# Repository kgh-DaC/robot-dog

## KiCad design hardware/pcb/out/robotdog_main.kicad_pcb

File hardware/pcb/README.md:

# 로봇개 메인 보드 PCB (50 × 70 mm, 2층)

`회로도.jpg`(Fritzing 배선도)를 기판 하나로 옮긴 것이다. 모듈(ESP32 30핀 DevKit, MPU9250, INA219, Mini360 ×3)은 그대로 꽂거나 납땜하고, 서보 12개는 3핀 헤더로 연결한다.

| 파일 | 용도 |
| --- | --- |
| `make_pcb.py` | 부품 연결·배치·배선이 모두 들어 있는 생성 스크립트. 실행하면 아래 파일을 다시 만들고 간격·연결 검사를 한다 |
| `out/robotdog_main_gerber.zip` | **PCB 주문용** (Gerber 7장 + 드릴 2장). JLCPCB 등에 그대로 올린다 |
| `out/robotdog_main.kicad_pcb` | KiCad 8에서 열어 고칠 수 있는 보드 파일 (GND 면은 열고 `B` 키로 채움) |
| `out/robotdog_main_top.png`, `_bottom.png` | 미리보기 (주황 = 윗면 구리, 파랑 = 아랫면 구리, 점선 = ESP32 보드 위치) |

**v2 (2026-11-16)**: ESP32를 30핀 보드(핀 줄 간격 25.4 mm, 사용자 확인)로 바꿈. 서보 헤더마다 관절 표시 추가.

다시 만들기: `pip install shapely matplotlib` 후 `python make_pcb.py`. 마지막 줄이 `DRC: no clearance / connectivity errors`여야 한다.

## 회로 (회로도.jpg와 같음, 바뀐 점은 굵게)

```
배터리(2×18650) + ─ 스위치(기판 밖) ─ J1 + ─ INA219 VIN+ ─(션트)─ VIN- ─┬─ PS1 Mini360 → 5.2 V → ESP32 VIN 핀, C1
배터리 -  ─────────────────────────── J1 - (GND)                        ├─ PS2 Mini360 → 6 V → 왼쪽 서보 6개(LF, LH), C2
                                                                         └─ PS3 Mini360 → 6 V → 오른쪽 서보 6개(RF, RH), C3
ESP32 3V3 → MPU9250 VCC, INA219 VCC        I2C: SDA = GPIO21, SCL = GPIO22 (MPU9250, INA219 공용)
MPU9250 AD0 → GND  (요청대로 선을 추가함. 주소 0x68 고정)
```

- **AD0-GND**: 윗면에 MPU9250 AD0 핀에서 같은 모듈의 GND 핀까지 배선이 있다 (핀 줄 왼쪽으로 돌아감). 실크에 `AD0=GND`라고 적혀 있다. INA219(0x40)와 주소가 겹치지 않는다.
- **추가한 것**: 서보 전원마다 1000 µF 콘덴서(C2, C3). 기록상 `reset=BROWNOUT`이 잦아서 넣었다. 필요 없으면 비워 둬도 된다.
- **스위치**: 회로도처럼 기판 밖에 둔다. 배터리 +는 스위치로 가고, 스위치 다른 쪽을 J1 +에 연결한다.

### 서보 핀 (펌웨어 `servoInitPose.ino`의 `servos[]` 그대로)

| 다리 | ALPHA | BETA | GAMMA | 기판 위치 |
| --- | --- | --- | --- | --- |
| LF (왼앞) | 25 | 26 | 27 | 왼쪽 헤더 위 3개 |
| LH (왼뒤) | 13 | 12 | 14 | 왼쪽 헤더 아래 3개 |
| RF (오른앞) | 16 | 18 | 17 | 오른쪽 헤더 위 3개 |
| RH (오른뒤) | 4 | 2 | 15 | 오른쪽 헤더 아래 3개 |

헤더 핀 순서: 안쪽(ESP32 쪽)부터 **S(신호) · + · -**. 서보 커넥터의 갈색(또는 검은색) 선이 바깥쪽 `-`로 가야 한다.

실크 표시: 헤더마다 안쪽에 **관절 글자 + GPIO** (`A25` = ALPHA·GPIO25, `B` = BETA, `G` = GAMMA). 바깥 가장자리에 다리 이름(LF, LH, RF, RH)이 있고, 두 다리 묶음 사이에 짧은 가로선이 있다. 왼쪽 아래에 `A:ALPHA B:BETA G:GAMMA` 설명이 있다.

| 헤더 | 위 → 아래 |
| --- | --- |
| 왼쪽 | LF: A25 B26 G27 ─ LH: G14 B12 A13 |
| 오른쪽 | RF: B18 (빈 칸) G17 A16 ─ RH: A4 B2 G15 |

## 부품 목록

| 기호 | 부품 | 수량 | 비고 |
| --- | --- | --- | --- |
| U1 | ESP32 DevKit V1 30핀 + 1×15 암 헤더 | 1 + 2 | 두 줄 간격 25.4 mm. 암 헤더 위에 꽂는다 (아래에 PS1, MPU9250이 들어감) |
| U2 | MPU9250 모듈 (GY-9250) | 1 | 1×10 수 헤더로 바로 납땜 |
| U3 | INA219 모듈 (Adafruit 904 핀 순서) | 1 | 1×6 수 헤더로 바로 납땜. **나사 단자는 달지 않는다** |
| PS1–PS3 | Mini360 강압 모듈 | 3 | 짧은 철사 다리(저항 다리 자투리)로 납땜 |
| J1 | 2핀 나사 단자 3.5 mm (KF350-2P) | 1 | 배터리 입력 (스위치 뒤) |
| J2–J13 | 1×3 수 핀 헤더 2.54 mm | 12 | 서보 |
| C1 | 470 µF 10 V 전해 (지름 6.3 mm, 높이 8 mm 이하) | 1 | ESP32 아래에 들어가므로 낮은 것 |
| C2, C3 | 1000 µF 10 V 전해 (지름 8 mm) | 2 | 선택 |
| H1–H3 | M3 장착 구멍 | 3 | 오른쪽 아래 모서리는 J1이 차지 |

기판 주문 설정: 2층, 1.6 mm, 구리 1 oz, 최소 선폭·간격 0.3 mm, 비아 0.4/0.8 mm. 전원선 폭은 2.0 mm(배터리·강압 입력), 1.5–2.0 mm(서보 전원, 위·아래 두 층), 1.0 mm(5 V)다.

## 꼭 확인할 것 (추정한 치수)

모듈 치수는 판매처마다 다르다. **주문 전에 갖고 있는 모듈을 자로 재서** 아래 값과 맞는지 본다. 다르면 `make_pcb.py` 앞부분 숫자를 고쳐 다시 실행한다.

1. **ESP32 30핀 보드**: 두 핀 줄 간격 25.4 mm (사용자 실측 확인). 핀 배열은 안테나를 위로 두고 왼쪽 위부터 EN, VP, VN, 34, 35, 32, 33, 25, 26, 27, 14, 12, 13, GND, VIN / 오른쪽 위부터 23, 22, TX, RX, 21, 19, 18, 5, 17, 16, 4, 2, 15, GND, 3V3 이어야 한다.
2. **Mini360 패드 위치**: 17.2 × 11.2 mm 모듈에서 패드가 길이 방향 14.4 mm, 폭 방향 8.4 mm 간격이라고 가정했다. 패드를 크게(1.8 × 2.4 mm) 만들고 철사 다리로 잇게 해 1 mm 정도 차이는 흡수된다. 또 IN+와 OUT+가 같은 긴 변에 있다고 가정했다. 실크의 `IN`/`OUT`/`+` 표시와 모듈 뒷면 글씨를 맞춰서 단다.
3. **INA219 핀 순서**: Adafruit 순서(VCC, GND, SCL, SDA, VIN-, VIN+)다. 보라색 호환 모듈은 순서가 다를 수 있다. 다르면 다른 모듈을 쓰거나 스크립트의 `INA_PINS`를 고친다.
4. **MPU9250 핀 순서**: VCC, GND, SCL, SDA, EDA, ECL, AD0, INT, NCS, FSYNC (GY-9250).

## 조립 순서와 안전

1. 빈 기판에서 테스터로 J1 +/-, 각 강압 출력이 GND와 붙어 있지 않은지 확인한다.
2. Mini360 세 개를 달고 **ESP32·센서·서보 없이** 배터리를 연결해 전압을 맞춘다. PS1 5.2 V, PS2·PS3 5.6–6 V. PS1은 ESP32 아래에 가려지므로 ESP32를 꽂기 전에 맞춘다.
3. 전원을 끈 뒤 MPU9250, INA219, 콘덴서, 헤더를 단다. C1·C2·C3의 `+` 방향을 확인한다.
4. ESP32를 꽂고 USB만 연결해 직렬 `I2C` 명령에 `0x40 0x68`이 나오는지 본다 (서보 전원은 아직 끈 상태).
5. 서보는 그 다음에 꽂는다. 처음 서보 전원을 넣을 때는 로봇을 들어 올린 상태에서, 스위치에 바로 손이 닿게 한다.

주의:
- **IMU 방향이 바뀐다.** MPU9250이 기판 위에서 세로로 놓이므로 기존 축 설정(rollmap=-Y, pitchmap=+X)과 영점은 새로 잡아야 한다.
- USB 케이블은 아래쪽(INA219 위)으로 나온다. INA219에 나사 단자를 달면 USB 플러그와 부딪힐 수 있어서 달지 않는다. 전류는 헤더의 VIN+/VIN- 핀으로 흐른다.
- INA219 모듈 션트(0.1 Ω)는 ±3.2 A까지만 정확하다. 서보 12개가 동시에 많이 당기면 그보다 커질 수 있다 (회로도와 같은 조건).
- ESP32 안테나 끝이 기판 위쪽 가장자리 밖으로 약 4 mm 나가도록 놓았다(30핀 보드의 핀-안테나 거리는 추정). 기판 안에 걸치는 부분(위쪽 2.5 mm 띠)에는 구리 면을 비웠다. 로봇에 고정할 때 안테나 위쪽을 금속으로 덮지 않는다.

## 검증한 것 / 안 한 것

- 한 것: 스크립트 자체 검사(서로 다른 신호 사이 구리 간격 ≥ 0.3 mm, 기판 가장자리 0.4 mm, 구멍 사이 간격, 21개 신호 모두 한 덩어리로 연결됨). 별도 Gerber 해석기(gerbonara)로 9개 파일을 모두 읽어 보았고, Gerber를 다시 도형으로 만들어 원래 설계와 면적이 일치함(오차 0.001 mm² 미만)을 확인했다.
- 안 한 것: KiCad로 직접 열어 보지 못했다 (이 PC에 KiCad가 없음). 실제 모듈 치수 실측, 기판 제작, 전원 투입 시험.

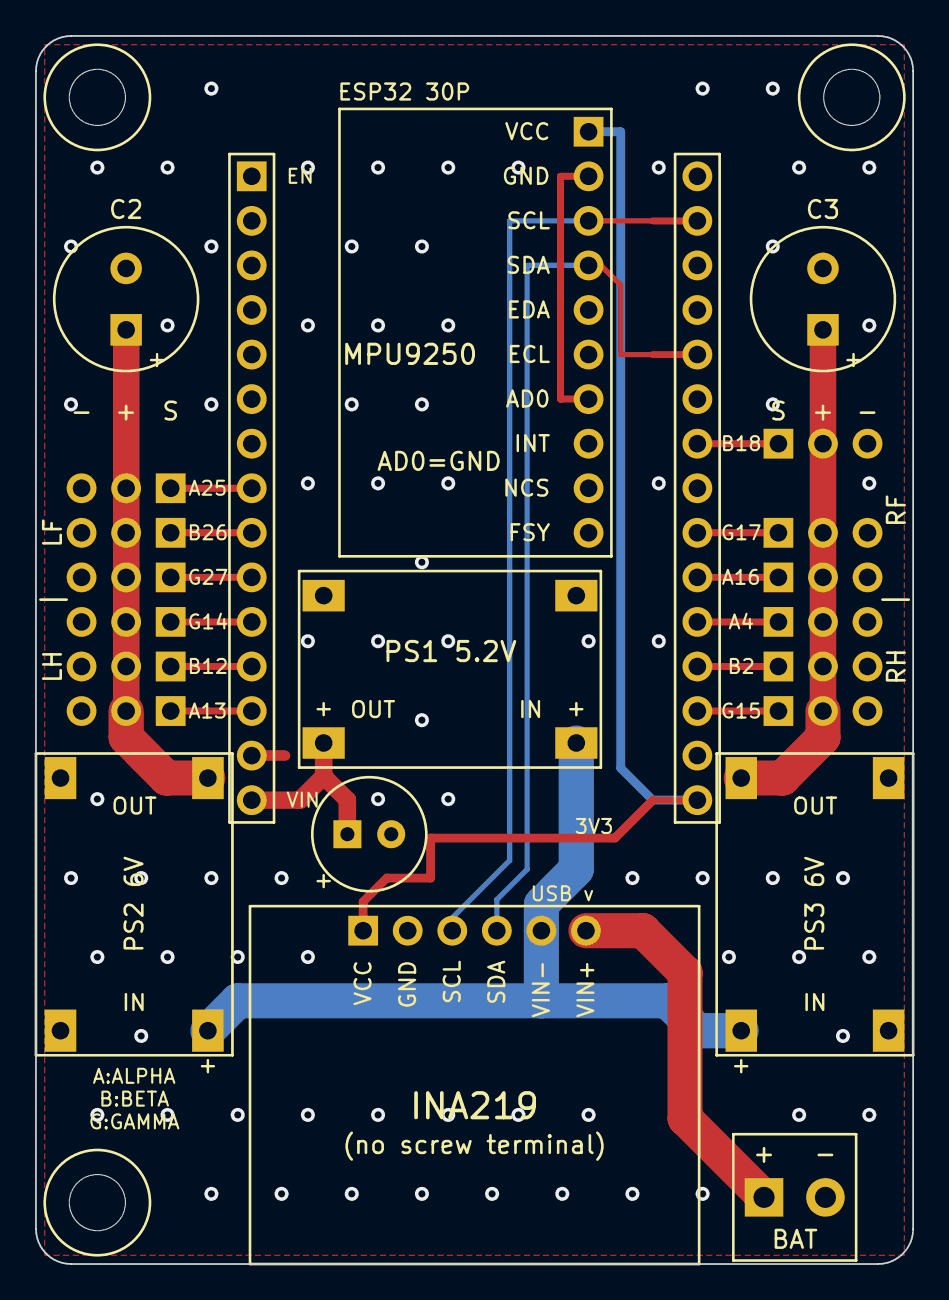
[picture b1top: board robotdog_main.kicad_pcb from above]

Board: 2 copper layers, 50.0 x 70.0 mm, 25 parts (0 on the bottom side), 21 nets.

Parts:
C1: 470uF 10V (6.3mm); C1_470uF
C2: 1000uF 10V (8mm); C2_1000uF
C3: 1000uF 10V (8mm); C3_1000uF
H1: M3; H1_M3
H2: M3; H2_M3
H3: M3; H3_M3
J1: BAT (after switch); J1_BAT
J2: Servo LF-A (IO25); J2_Servo
J3: Servo LF-B (IO26); J3_Servo
J4: Servo LF-G (IO27); J4_Servo
J5: Servo LH-G (IO14); J5_Servo
J6: Servo LH-B (IO12); J6_Servo
J7: Servo LH-A (IO13); J7_Servo
J8: Servo RF-B (IO18); J8_Servo
J9: Servo RF-G (IO17); J9_Servo
J10: Servo RF-A (IO16); J10_Servo
J11: Servo RH-A (IO4); J11_Servo
J12: Servo RH-B (IO2); J12_Servo
J13: Servo RH-G (IO15); J13_Servo
PS1: Mini360 -> 5.2V (ESP32); PS1_Mini360
PS2: Mini360 -> 6V (servo L); PS2_Mini360
PS3: Mini360 -> 6V (servo R); PS3_Mini360
U1: ESP32-DevKit-30P; U1_ESP32-DevKit-30P
U2: MPU9250 (GY-9250); U2_MPU9250
U3: INA219 module; U3_INA219

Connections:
+3V3: U1.30, U2.1, U3.1
+5V_ESP: C1.1, PS1.3, U1.15
+6V_SRV_L: C2.1, J2.2, J3.2, J4.2, J5.2, J6.2, J7.2, PS2.3
+6V_SRV_R: C3.1, J8.2, J9.2, J10.2, J11.2, J12.2, J13.2, PS3.3
GND: C1.2, C2.2, C3.2, J1.2, J2.3, J3.3, J4.3, J5.3, J6.3, J7.3, J8.3, J9.3, J10.3, J11.3, J12.3, J13.3, PS1.2, PS1.4, PS2.2, PS2.4, PS3.2, PS3.4, U1.14, U1.29, U2.2, U2.7, U3.2
SCL: U1.17, U2.3, U3.3
SDA: U1.20, U2.4, U3.4
SRV_LF_A_IO25: J2.1, U1.8
SRV_LF_B_IO26: J3.1, U1.9
SRV_LF_G_IO27: J4.1, U1.10
SRV_LH_A_IO13: J7.1, U1.13
SRV_LH_B_IO12: J6.1, U1.12
SRV_LH_G_IO14: J5.1, U1.11
SRV_RF_A_IO16: J10.1, U1.25
SRV_RF_B_IO18: J8.1, U1.22
SRV_RF_G_IO17: J9.1, U1.24
SRV_RH_A_IO4: J11.1, U1.26
SRV_RH_B_IO2: J12.1, U1.27
SRV_RH_G_IO15: J13.1, U1.28
VBAT_SW: J1.1, U3.6
VIN_BUCK: PS1.1, PS2.1, PS3.1, U3.5

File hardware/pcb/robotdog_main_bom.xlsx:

로봇개 메인 보드 부품 구매 목록
노란 칸만 고치세요: '보유 수량'에 지금 갖고 있는 개수, '단가(원)'에 살 곳의 가격을 넣으면 '구매 수량'과 '금액'이 계산됩니다. 보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
번호 | 구분 | 기호 | 부품 | 규격 | 기판 1장당 수량 | 권장 준비 수량 | 보유 수량 | 구매 수량 | 단가(원) | 금액(원) | 비고
1 | 기판 | PCB | 메인 보드 기판 | 50 × 70 mm, 2층, 1.6 mm, HASL, 녹색 | 1 | 5 | 0 |  |  |  | JLCPCB 장바구니에 담아 둠 (5장 $4.00 + E-POST $5.79). 최소 주문이 5장
2 | 기판에 납땜하는 부품 | U1 소켓 | 암 핀 헤더 1×15 | 2.54 mm, 1열 15핀 | 2 | 3 | 0 |  |  |  | ESP32를 꽂는 소켓. 1×40을 잘라 써도 됨. 높이 8.5 mm 일반형 (아래에 PS1·MPU9250이 들어감)
3 | 기판에 납땜하는 부품 | J2–J13, U2, U3 | 수 핀 헤더 1×40 | 2.54 mm, 1열 40핀 | 2 | 3 | 0 |  |  |  | 서보 12개 × 3핀 = 36핀, MPU9250 10핀, INA219 6핀 → 모두 52핀. 40핀짜리 2줄을 잘라 씀. 모듈에 헤더가 딸려 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
4 | 기판에 납땜하는 부품 | J1 | 나사 단자 2핀 | 3.5 mm 피치 (KF350-2P) | 1 | 2 | 0 |  |  |  | 배터리 입력. 5.0 / 5.08 mm 피치는 맞지 않음
5 | 기판에 납땜하는 부품 | C1 | 전해 콘덴서 470 µF | 10 V 이상, 지름 6.3 mm, 높이 8 mm 이하 | 1 | 2 | 0 |  |  |  | ESP32 아래에 들어가므로 낮은 것. 높이가 넘으면 눕혀서 단다
6 | 기판에 납땜하는 부품 | C2, C3 | 전해 콘덴서 1000 µF | 10 V 이상 (16 V 권장), 지름 8 mm | 2 | 3 | 0 |  |  |  | 서보 전원용, 선택 부품. 브라운아웃이 잦아 넣기를 권함
7 | 모듈 | U1 | ESP32 DevKit V1 30핀 | 핀 줄 간격 25.4 mm, CP210x | 1 | 1 | 1 |  |  |  | 지금 쓰는 보드를 옮겨 꽂음. 보유 수량은 추정이니 고칠 것
8 | 모듈 | U2 | MPU9250 모듈 (GY-9250) | 10핀, VCC GND SCL SDA EDA ECL AD0 INT NCS FSYNC | 1 | 1 | 1 |  |  |  | 지금 로봇의 센서를 옮겨도 됨. 핀 순서가 다른 모듈은 맞지 않음
9 | 모듈 | U3 | INA219 모듈 | 6핀, Adafruit 904 핀 순서 (VCC GND SCL SDA VIN- VIN+) | 1 | 1 | 1 |  |  |  | 보라색 호환 모듈은 핀 순서가 다를 수 있음: 사기 전에 확인. 나사 단자는 달지 않음
10 | 모듈 | PS1–PS3 | Mini360 강압 모듈 | 17.2 × 11.2 mm, 출력 가변 | 3 | 4 | 3 |  |  |  | 5.2 V 1개(ESP32), 6 V 2개(서보). 패드 간격 14.4 × 8.4 mm로 가정했으니 실측 확인. 보유 수량은 추정
11 | 전원·배선 | SW | 슬라이드 스위치 SS-12D06 | 정격 2~3 A 제품 | 1 | 1 | 1 |  |  |  | 기판 밖에 둠. 사용자가 보유 (정격 0.3 A짜리면 부족)
12 | 전원·배선 | - | 실리콘 전선 | 20 AWG 이상(굵게), 빨강·검정 각 1 m | 1 | 1 | 0 |  |  |  | 배터리 → 스위치 → J1. 서보 12개 전류가 흐르므로 가는 점퍼선은 쓰지 않음
13 | 전원·배선 | - | 18650 배터리 2개 + 2구 홀더 | 직렬 7.4 V, 보호회로 권장 | 1 | 1 | 1 |  |  |  | 지금 쓰는 것을 그대로 사용. 보유 수량은 추정
14 | 고정 | H1–H3 | M3 나사 + 스페이서 | M3 × 6 mm 나사, 스페이서 6~10 mm | 3 | 4 | 0 |  |  |  | 장착 구멍 3개. 나일론 스페이서 권장
15 | 조립 소모품 | - | 실납 | 지름 0.6~0.8 mm | 1 | 1 | 0 |  |  |  | 없을 때만 구매
16 | 조립 소모품 | - | 철사 다리 (저항 다리 자투리) | 지름 약 0.5 mm, 12가닥 | 1 | 1 | 0 |  |  |  | Mini360을 기판에 잇는 데 씀. 핀 헤더에서 뽑은 핀으로 대신해도 됨
 |  |  | 합계 |  |  |  |  |  |  |  | 금액 합계는 단가를 넣은 줄만 더합니다. 기판(JLCPCB)은 달러로 따로 결제합니다.
참고
· 출처: hardware/pcb/README.md의 부품 목록과 make_pcb.py의 기판 설계 (2026-11-16 v2).
· 권장 준비 수량은 납땜 실수에 대비한 여분 1개를 더한 값입니다. 여분이 필요 없으면 '기판 1장당 수량'만큼만 사도 됩니다.
· 서보 12개는 지금 로봇에 달린 것을 그대로 쓰므로 목록에 넣지 않았습니다.
· 사기 전에 실측할 것: Mini360 패드 간격(14.4 × 8.4 mm 가정), INA219 핀 순서(Adafruit 순서 가정), ES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
